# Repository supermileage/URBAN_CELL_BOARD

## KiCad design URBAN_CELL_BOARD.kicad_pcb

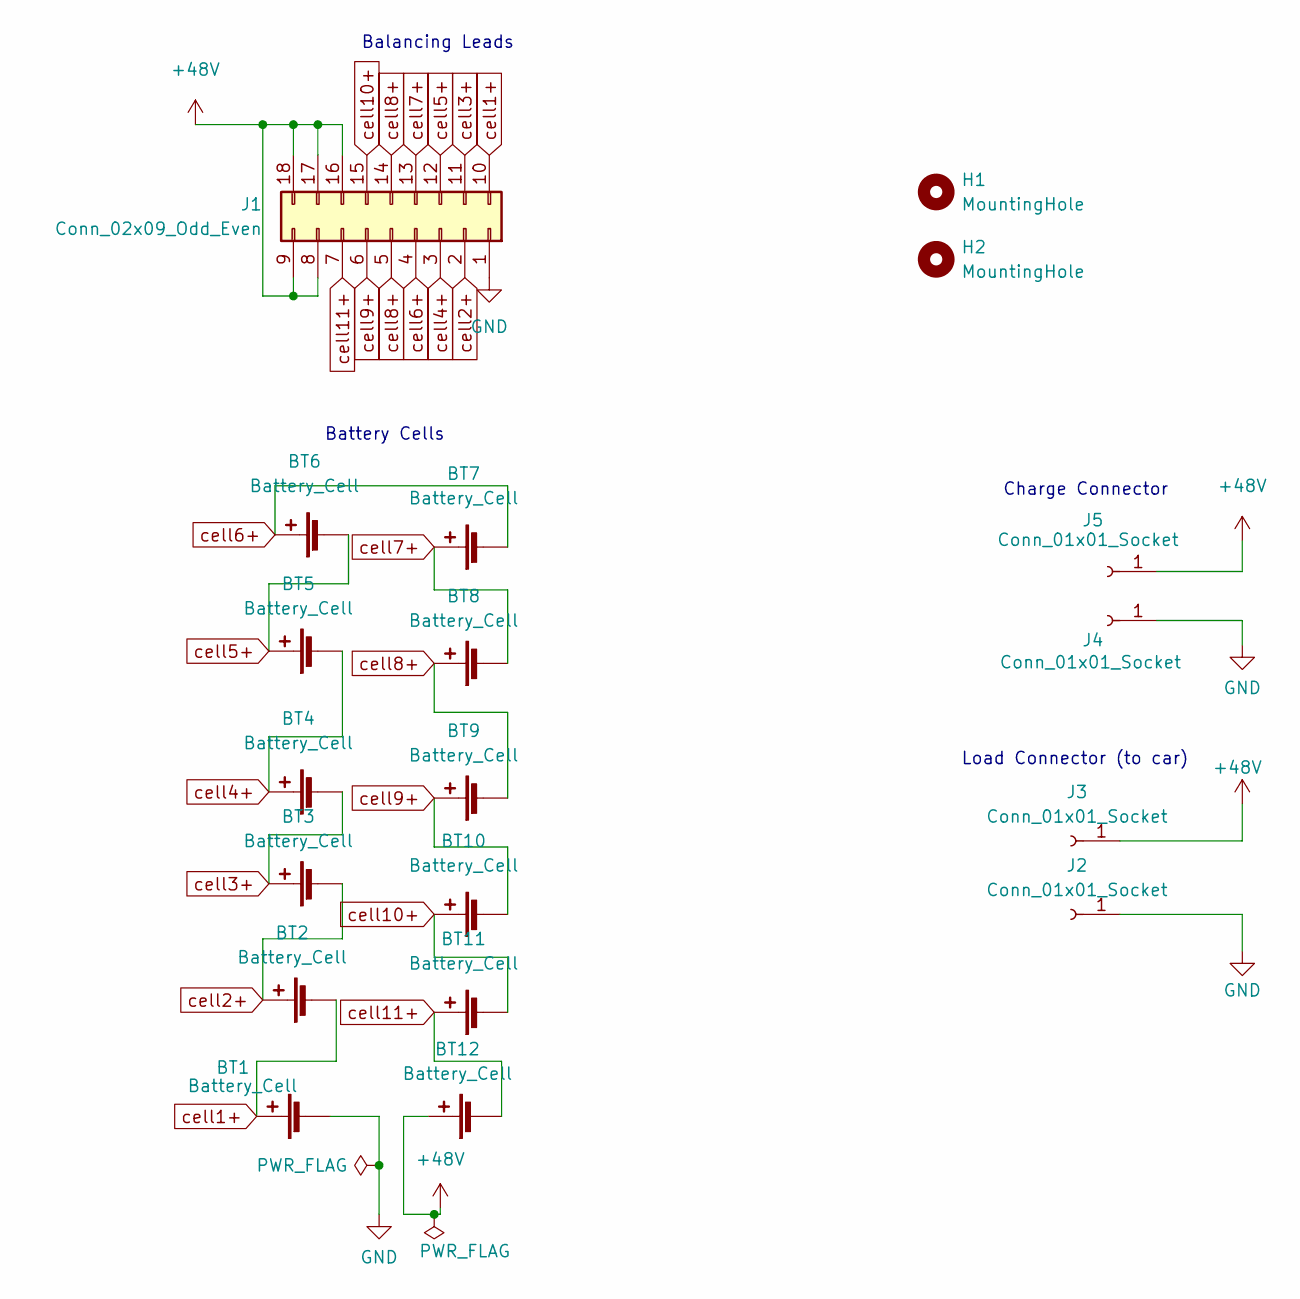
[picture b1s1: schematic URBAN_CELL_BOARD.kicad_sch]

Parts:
BT1, BT2, BT3, BT4, BT5, BT6, BT7, BT8, BT9, BT10, BT11, BT12: Battery_Cell; Energus Li1x4pVTC6T
H1, H2: MountingHole; MountingHole_8.4mm_M8
J1: Conn_02x09_Odd_Even; Molex_Mini-Fit_Jr_5569-18A2_2x09_P4.20mm_Horizontal
J2, J3: Conn_01x01_Socket; AMP_01x01_WTB036SV061250R_RADSOKPOWERLOK
J4, J5: Conn_01x01_Socket; PHOENIX_01x01_1190362_TERMBLOCK_ANGLED

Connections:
+48V: BT12.1 (+), J1.8, J1.9, J1.16, J1.17, J1.18, J3.1, J5.1
GND: BT1.2 (-), J1.1, J2.1, J4.1
cell1+: BT1.1 (+), BT2.2 (-), J1.10
cell2+: BT2.1 (+), BT3.2 (-), J1.2
cell3+: BT3.1 (+), BT4.2 (-), J1.11
cell4+: BT4.1 (+), BT5.2 (-), J1.3
cell5+: BT5.1 (+), BT6.2 (-), J1.12
cell6+: BT6.1 (+), BT7.2 (-), J1.4
cell7+: BT7.1 (+), BT8.2 (-), J1.13
cell8+: BT8.1 (+), BT9.2 (-), J1.5, J1.14
cell9+: BT9.1 (+), BT10.2 (-), J1.6
cell10+: BT10.1 (+), BT11.2 (-), J1.15
cell11+: BT11.1 (+), BT12.2 (-), J1.7

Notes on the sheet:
Balancing Leads
Load Connector (to car)
Battery Cells
Charge Connector

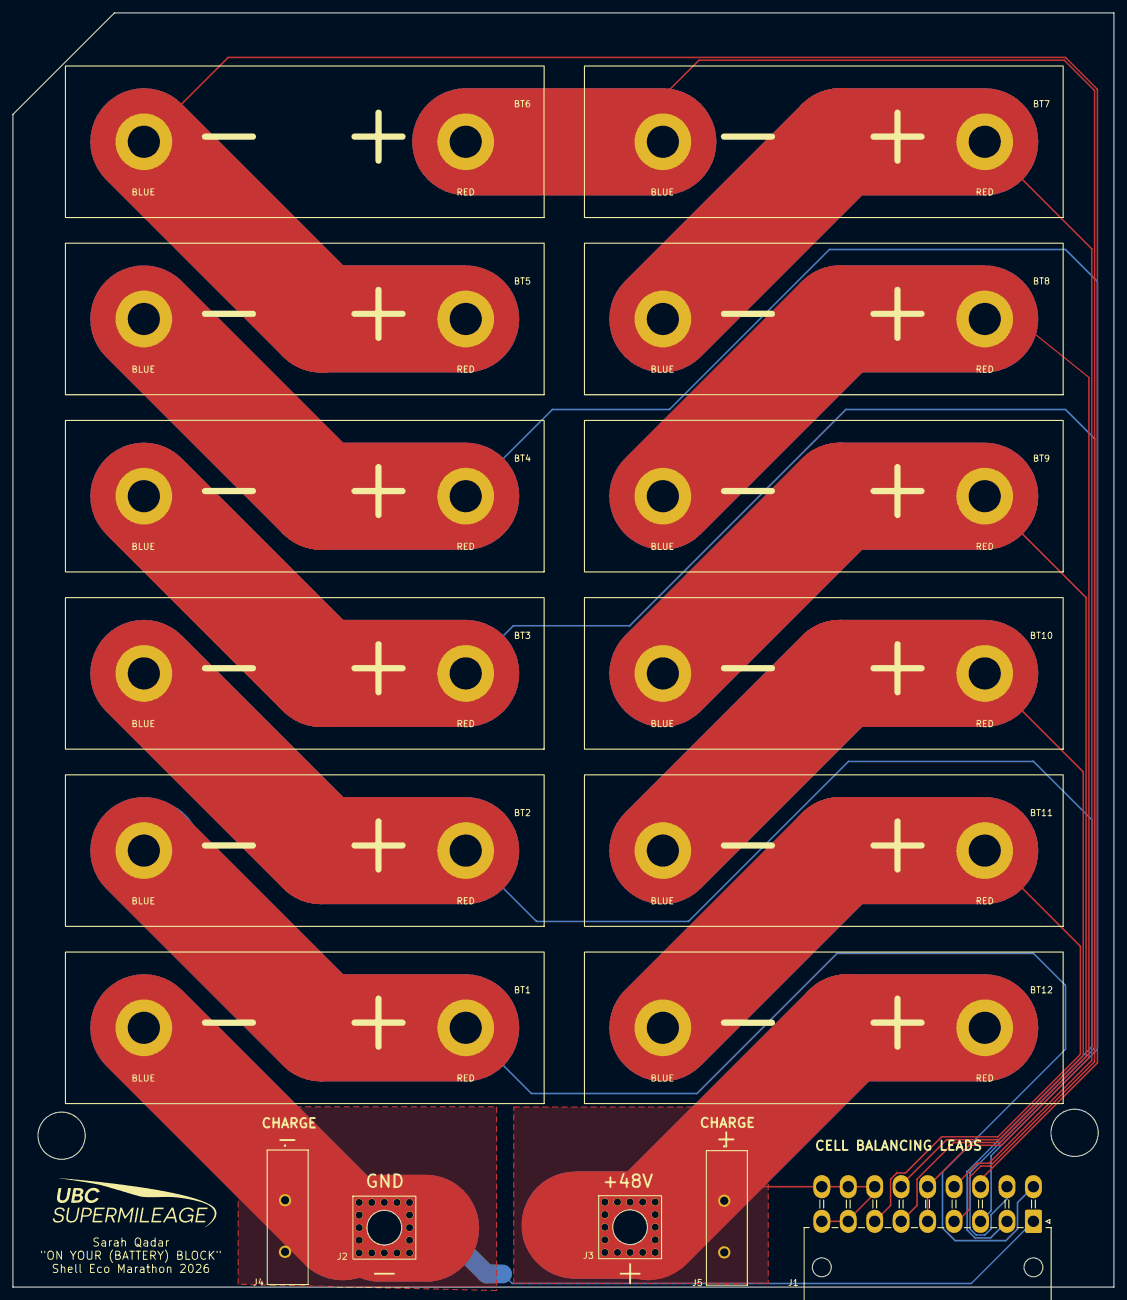
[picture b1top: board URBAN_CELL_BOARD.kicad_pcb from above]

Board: 2 copper layers, 174.8 x 202.3 mm, 19 parts (0 on the bottom side), 13 nets.

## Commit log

2022-11-12 created kicad project
2022-11-13 completed schematic and specced components
2022-12-04 most of layout done and custom footprints made for battery blocks
2022-12-10 fixed connector footprints, edited connector symbols, added mounting holes, solved DRC routing issue, created 48V and GND filled zones around one connector, made silkscreen edits
2022-12-24 routed traces
2022-12-26 fixed most layout errors/warnings
2022-12-26 edited silkscreen
2022-12-27 fixes some cell positions
2022-12-30 genersated gerber file
2023-02-25 replaced charge terminal with two larger single position ones, fixed labelling
2023-02-27 completed edits
2023-03-05 generated drill file and gerbers in gerbers2.0 folder
2024-10-12 just pushing to verify no accidental changes were made before more people work on this again
2024-10-28 start adding power element
2024-11-09 Created charge conn footprints. Updated main conn footprints. Assigned 3D models to charge and main conn. Changed charge conn symbols. Updated datasheets. Consolidated custom footprints back into cor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
2024-11-09 Fixed footprint for all Wurth Elec 36 pin connectors such that all pins would be connected. Edited layout
2024-11-11 Added 3D models for J1, J4 and J5
2024-11-13 Final touches to pcb layout. Generated gerber, drill and drill map files in gerbers2.1 folder
2025-02-08 Replaced load and charge connectors with new parts
2025-02-18 Added 3D models for connectors, renamed board, updated silkscreen labels, adjusted connector spacing, generated gerber, drill and drill map files
2025-11-01 added custom footprint and 3d model for the new cell
2025-11-22 new PCB layout with new cell footprint
2025-12-19 updated footprint again with traces
2025-12-21 changed year, generated gerber and drill
